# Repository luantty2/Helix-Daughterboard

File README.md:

## Helix Daughterboard
The helix daughterboard is a USB breakout board designed specifically for keyboards. The board integrates 11 components in a relatively small-sized PCB, and it's able to provide full protection for USB2.0 interface.

### FEATURES

* IEC 61000-4-2 Level 4 ESD Protection
* VBUS UVLO, OVLO, OCP

### DEATILS

* J1 is the USB3.0 receptacle with a row of through-hole data pins, with which the receptacle can be soldered much more firmly. In addition, C1 must have the rated voltage ≥2KV.

* U1 is the ONsemi NCP361, which is a single-chip solution for Undervoltage Lockout(UVLO), Overvoltage Lockout(OVLO) and Overcurrent Protection(OCP). 

    The overvoltage lockout threshold is typically 5.675V and overcurrent limit is internally set to 750mA. 

    The NCP361 itself complies to IEC61000−4−2 (Level 4), so place the device before U3 to keep VBUS voltage not violating TPD1E10B06's DC breakdown voltage(±6V).

* U2 is TPD4E05U06 ESD and surge protection chip for USB data lines and CC pins.

* U3 is TPD1E10B06 ESD and surge protection chip for VBUS power.

* H1 and H2 are screw mounting holes, one of them is connected to USB shield.

### BOM

| Designator  | Comment         | Package    | LCSC PN    |
| ----------- | -----------     | ---------- | ---------- |
| C1          | 1nF             | 1210       | C173219
| C2          | 2.2uF           | 0603       | C342993
| C3          | 1uF             | 0603       | C76619
| J2          | SM04B-SRSS-TB   | -          | C160404
| R1          | 1M              | 1206       | C205050
| R2, R3      | 5.1K            | 0402       | C203181
| U1          | NCP361          | UDFN-6     | C233713
| U2          | TPD4E05U06DQAR  | USON-10    | C138714
| U3          | TPD1E10B06      | X1SON-2    | C48260
| J1          | U262-241N-4BV60 | -          | C388659

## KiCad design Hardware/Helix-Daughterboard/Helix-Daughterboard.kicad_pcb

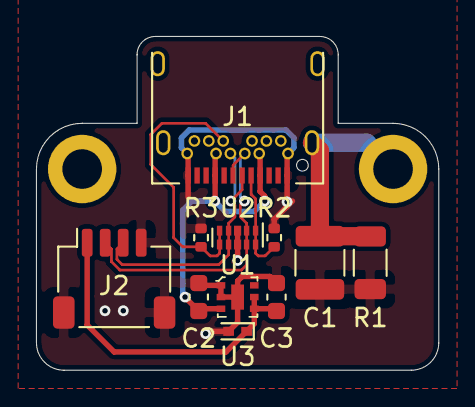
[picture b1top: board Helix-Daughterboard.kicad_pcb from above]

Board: 2 copper layers, 22.4 x 18.5 mm, 13 parts (0 on the bottom side), 8 nets.

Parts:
C1: 1n; C_1210_3225Metric
C2: 2.2u; C_0603_1608Metric
C3: 1u; C_0603_1608Metric
H1, H2: M2; MountingHole_2.2mm_M2_DIN965_Pad
J1: U262-241N-4BV60; USB3_C_Receptacle_HRO
J2: SM04B-SRSS-TB; JST_SH_SM04B-SRSS-TB_1x04-1MP_P1.00mm_Horizontal
R1: 1M; R_1206_3216Metric
R2, R3: 5.1K; R_0402_1005Metric
U1: NCP361; UDFN-6-1EP_2x2mm
U2: TPD4E05U06DQAR; USON-10_2.5x1.0mm_P0.5mm
U3: TPD1E10B06; X1SON-2

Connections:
/5V: C3.1, J2.1, U1.4, U1.5, U3.1
/USBC_CC1: J1.A5, R2.1, U2.1, U2.10
/USBC_CC2: J1.B5, R3.1, U2.5, U2.6
/USBC_DN: J1.A7, J1.B7, J2.2, U2.2, U2.9
/USBC_DP: J1.A6, J1.B6, J2.3, U2.4, U2.7
Earth: C1.2, H2.1, J1.S1, R1.2
GND: C1.1, C2.2, C3.2, J1.A1, J1.A12, J1.B1, J1.B12, J2.4, J2.MP, R1.1, R2.2, R3.2, U1.1, U1.2, U1.7, U2.3, U2.8, U3.2
VBUS: C2.1, J1.A4, J1.A9, J1.B4, J1.B9, U1.3

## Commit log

2021-01-17 inital commit
2021-01-17 fix image
